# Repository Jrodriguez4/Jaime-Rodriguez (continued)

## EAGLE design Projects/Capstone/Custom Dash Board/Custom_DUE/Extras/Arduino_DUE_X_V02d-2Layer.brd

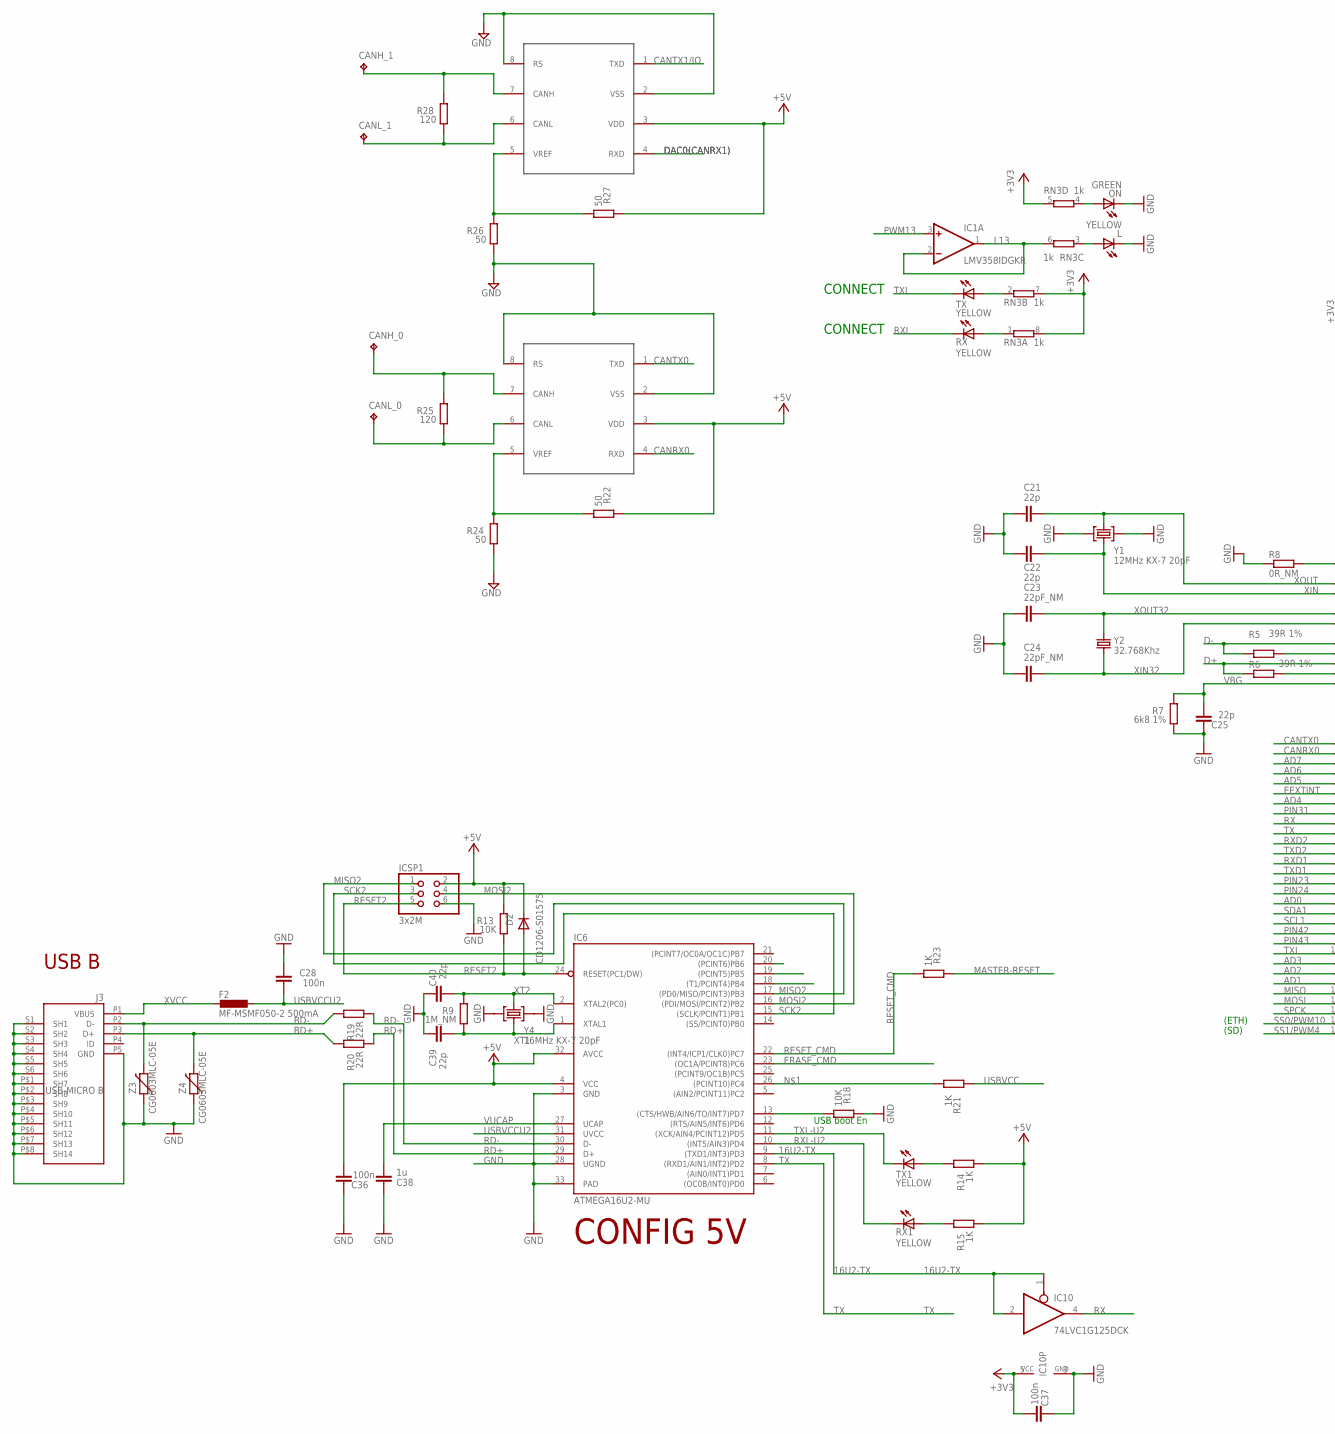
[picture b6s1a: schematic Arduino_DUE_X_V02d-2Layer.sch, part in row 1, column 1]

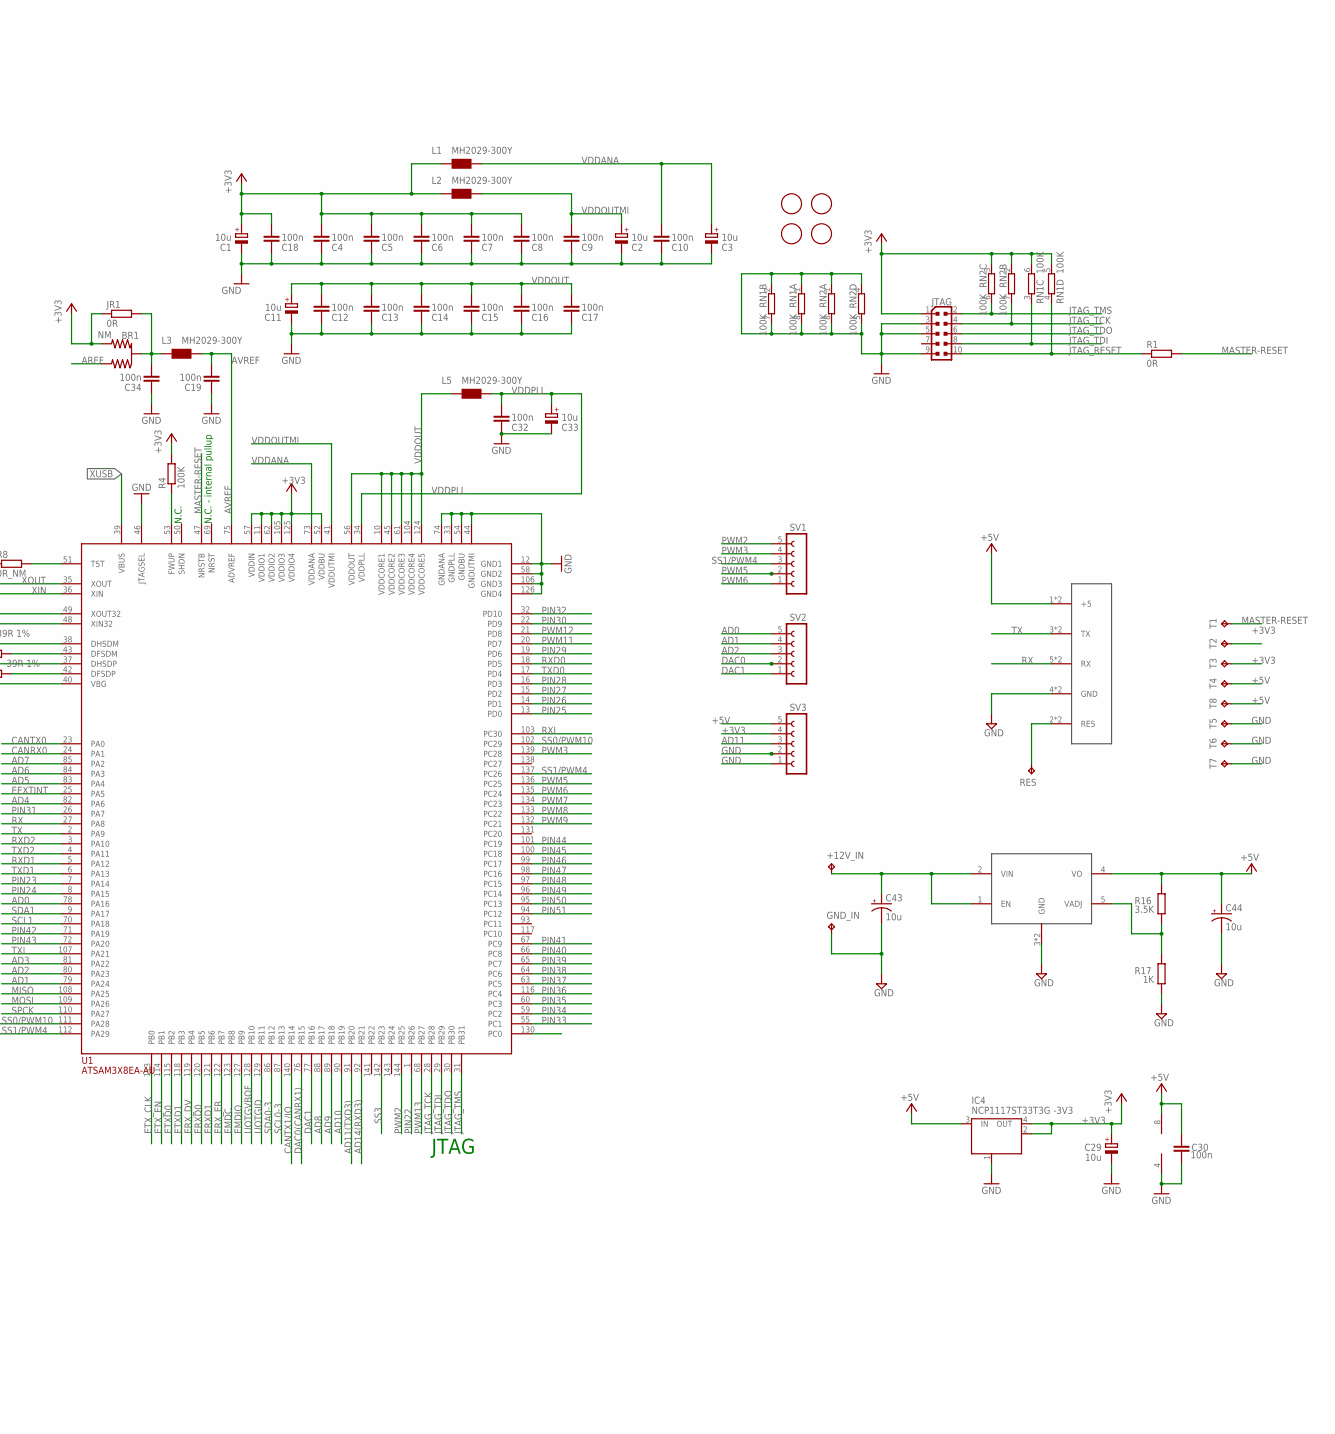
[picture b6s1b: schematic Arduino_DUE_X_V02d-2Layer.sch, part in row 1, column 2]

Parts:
+12V_IN: TPPAD1-13; P1-13
BR1: NM; J0402
C1, C2, C3, C11, C29, C33: 10u; SMC_B
C4, C5, C6, C7, C8, C9, C10, C12, C13, C14, C15, C16, C17, C18, C19, C28, C30, C32, C34, C36, C37: 100n; C0805
C21, C22, C25, C39, C40: 22p; C0805
C23, C24: 22pF_NM; C0805
C38: 1u; C0805
C43, C44: 10u; 153CLV-0405
CANH_0, CANH_1: TPPAD1-13; P1-13
CANL_0, CANL_1: TPPAD1-13; P1-13
D2: CD1206-S01575; MINIMELF
F2: MF-MSMF050-2 500mA; L1812
FID1, FID2, FID3, FID4: FIDUCIALMOUNT; FIDUCIA-MOUNT
GND_IN: TPPAD1-13; P1-13
IC1: LMV358IDGKR; MSOP08
IC4: NCP1117ST33T3G -3V3; SOT223
IC6: ATMEGA16U2-MU; MLF32
IC10: 74LVC1G125DCK; SC70-5
ICSP1: 3x2M; 2X03
J3: USB-MICRO B; CON2_USB_MICRO_B_AT
JR1: 0R; R0805
JTAG: PINHEAD_PINHD-2X5PASSO127; PINHEAD_2X05_127
L: YELLOW; CHIP-LED0805
L1, L2, L3, L5: MH2029-300Y; 0805
ON: GREEN; CHIP-LED0805
R1: 0R; R0805
R4: 100K; R0805
R5, R6: 39R 1%; R0805
R7: 6k8 1%; R0805
R8: 0R_NM; R0805
R9: 1M_NM; R0805
R13, R18: 10K; R0805
R14, R15, R17, R21, R23: 1K; R0805
R16: 3.5K; R0805
R19, R20: 22R; R0805
R22, R24, R26, R27: 50; R0805
R25, R28: 120; R0805
RES: TPB1,27; B1,27
RN1, RN2: 100K; CAT16
RN3: 1k; CAY16
RX, RX1: YELLOW; CHIP-LED0805
SV1, SV2, SV3: FE05-1
T1, T3, T4, T5, T8: TPB1,27; B1,27
T2: TPTP10R; TP10R
T6, T7: TPTP20SQ; TP20SQ
TX, TX1: YELLOW; CHIP-LED0805
U1: ATSAM3X8EA-AU; LQFP144
U2, U4: MCP2551; SOIC8
U3: LCD_DISPLAY; FE05-2
U$1: TLF1963TBATMA1; DPAK
Y1: 12MHz KX-7 20pF; CRYSTAL-3.2-2.5
Y2: 32.768Khz; RESONATOR_EPSON_FC_145
Y4: 16MHz KX-7 20pF; CRYSTAL-3.2-2.5
Z3, Z4: CG0603MLC-05E; CT/CN0805

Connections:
8PB4: IC6.18 ((T1/PCINT4)PB4)
8PB5: IC6.19 ((PCINT5)PB5)
8PB6: IC6.20 ((PCINT6)PB6)
16U2-TX: IC6.9 ((TXD1/INT3)PD3), IC10.1 (OE), IC10.2 (I)
+3V3: BR1.3 (2), C1.+, C4.2, C5.2, C6.2, C7.2, C8.2, C18.2, C29.+, C37.1, IC4.2 (OUT), IC4.4 (OUT), IC10.5 (VCC), JR1.1, JTAG.1, L1.1, L2.1, R4.2, RN1.5 (2), RN1.6 (2), RN2.2 (1), RN2.3 (1), RN3.5 (2), RN3.7 (2), RN3.8 (2), SV3.4, T2.TP, T3.TP, U1.11 (VDDIO1), U1.52 (VDDBU), U1.57 (VDDIN), U1.62 (VDDIO2), U1.105 (VDDIO3), U1.125 (VDDIO4)
+5V: C30.2, C36.1, C44.+, D2.C, IC1.8 (V+), IC4.3 (IN), IC6.4 (VCC), IC6.32 (AVCC), ICSP1.2, R13.2, R14.1, R15.1, R16.2, R22.2, R27.2, SV3.5, T4.TP, T8.TP, U2.3 (VDD), U3.1 (+5), U3.10 (+5), U4.3 (VDD), U$1.4 (VO)
AD0: SV2.5, U1.78 (PA16)
AD1: SV2.4, U1.79 (PA24)
AD2: SV2.3, U1.80 (PA23)
AD3: U1.81 (PA22)
AD4: U1.82 (PA6)
AD5: U1.83 (PA4)
AD6: U1.84 (PA3)
AD7: U1.85 (PA2)
AD8: U1.88 (PB17)
AD9: U1.89 (PB18)
AD10: U1.90 (PB19)
AD11: SV3.3
AD11(TXD3): U1.91 (PB20)
AD14(RXD3): U1.92 (PB21)
AREF: BR1.1
AVREF: C19.2, L3.2, U1.75 (ADVREF)
AVREFL: BR1.2 (C), C34.2, JR1.2, L3.1
BD+: J3.P3 (D+), R20.2, Z4.2
BD-: J3.P2 (D-), R19.2, Z3.2
CANRX0: U1.24 (PA1), U4.4 (RXD)
CANTX0: U1.23 (PA0), U4.1 (TXD)
CANTX1/IO: U1.140 (PB14), U2.1 (TXD)
D+: R6.1, U1.37 (DHSDP)
D-: R5.1, U1.38 (DHSDM)
DAC0: SV2.2
DAC0(CANRX1): U1.76 (PB15), U2.4 (RXD)
DAC1: SV2.1, U1.77 (PB16)
DTR: IC6.13 ((CTS/HWB/AIN6/TO/INT7)PD7), R18.1
EEXTINT: U1.25 (PA5)
EMDC: U1.123 (PB8)
EMDIO: U1.127 (PB9)
ERASE_CMD: IC6.23 ((OC1A/PCINT8)PC6)
ERASE_S: U1.130 (PC0)
ERXD0: U1.120 (PB5)
ERXD1: U1.121 (PB6)
ERX_DV: U1.119 (PB4)
ERX_ER: U1.122 (PB7)
ETXD0: U1.115 (PB2)
ETXD1: U1.118 (PB3)
ETX_CLK: U1.113 (PB0)
ETX_EN: U1.114 (PB1)
GND: C1.-, C2.-, C3.-, C4.1, C5.1, C6.1, C7.1, C8.1, C9.1, C10.1, C11.-, C12.1, C13.1, C14.1, C15.1, C16.1, C17.1, C18.1, C19.1, C21.2, C22.2, C23.2, C24.2, C25.2, C28.2, C29.-, C30.1, C32.1, C33.-, C34.1, C36.2, C37.2, C38.2, C39.2, C40.2, C43.-, C44.-, GND_IN.TP, IC1.4 (V-), IC4.1 (GND/ADJ), IC6.3 (GND), IC6.28 (UGND), IC6.33 (PAD), IC10.3 (GND), ICSP1.6, J3.P5 (GND), J3.P$1 (SH7), J3.P$2 (SH8), J3.P$3 (SH9), J3.P$4 (SH10), J3.P$5 (SH11), J3.P$6 (SH12), J3.P$7 (SH13), J3.P$8 (SH14), J3.S1 (SH1), J3.S2 (SH2), J3.S3 (SH3), J3.S4 (SH4), J3.S5 (SH5), J3.S6 (SH6), JTAG.3, JTAG.5, JTAG.9, L.C, ON.C, R7.1, R8.1, R17.1, R18.2, R24.1, R26.1, RN1.1, RN1.2 (1), RN1.7 (2), RN1.8 (2), RN2.1, RN2.4 (1), RN2.5 (2), RN2.8 (2), SV3.1, SV3.2, T5.TP, T6.TP, T7.TP, U1.12 (GND1), U1.33 (GNDPLL), U1.44 (GNDUTMI), U1.46 (JTAGSEL), U1.54 (GNDBU), U1.58 (GND2), U1.74 (GNDANA), U1.106 (GND3), U1.126 (GND4), U2.2 (VSS), U2.8 (RS), U3.4 (GND), U3.7 (GND), U4.2 (VSS), U4.8 (RS), U$1.3 (GND), U$1.6 (GND), Y1.2 (GND), Y1.4 (GND), Y4.2 (GND), Y4.4 (GND), Z3.1, Z4.1
JTAG_RESET: JTAG.10, R1.1, RN1.4 (1)
JTAG_TCK: JTAG.4, RN2.7 (2), U1.28 (PB28)
JTAG_TDI: JTAG.8, RN1.3 (1), U1.29 (PB29)
JTAG_TDO: JTAG.6, U1.30 (PB30)
JTAG_TMS: JTAG.2, RN2.6 (2), U1.31 (PB31)
L13: IC1.1 (OUT), IC1.2 (-IN), RN3.6 (2)
MASTER-RESET: R1.2, R23.2, T1.TP, U1.47 (NRSTB)
MISO: U1.108 (PA25)
MISO2: IC6.17 ((PD0/MISO/PCINT3)PB3), ICSP1.1
MOSI: U1.109 (PA26)
MOSI2: IC6.16 ((PDI/MOSI/PCINT2)PB2), ICSP1.4
unnamed: IC6.26 ((PCINT10)PC4), R21.1
unnamed: L.A, RN3.3 (1)
unnamed: ON.A, RN3.4 (1)
unnamed: R15.2, RX1.A
unnamed: R8.2, U1.51 (TST)
unnamed: R4.1, U1.53 (FWUP)
unnamed: R5.2, U1.43 (DFSDM)
unnamed: R6.2, U1.42 (DFSDP)
unnamed: +12V_IN.TP, C43.+, U$1.1 (EN), U$1.2 (VIN)
unnamed: R14.2, TX1.A
unnamed: R16.1, R17.2, U$1.5 (VADJ)
unnamed: R26.2, R27.1, U2.5 (VREF)
unnamed: R22.1, R24.2, U4.5 (VREF)
unnamed: CANH_0.TP, R25.2, U4.7 (CANH)
unnamed: CANL_0.TP, R25.1, U4.6 (CANL)
unnamed: RES.TP, U3.2 (RES), U3.9 (RES)
unnamed: CANH_1.TP, R28.2, U2.7 (CANH)
unnamed: CANL_1.TP, R28.1, U2.6 (CANL)
unnamed: RN3.1, RX.A
unnamed: RN3.2 (1), TX.A
PIN22: U1.1 (PB26)
PIN23: U1.7 (PA14)
PIN24: U1.8 (PA15)
PIN25: U1.13 (PD0)
PIN26: U1.14 (PD1)
PIN27: U1.15 (PD2)
PIN28: U1.16 (PD3)
PIN29: U1.19 (PD6)
PIN30: U1.22 (PD9)
PIN31: U1.26 (PA7)
PIN32: U1.32 (PD10)
PIN33: U1.55 (PC1)
PIN34: U1.59 (PC2)
PIN35: U1.60 (PC3)
PIN36: U1.116 (PC4)
PIN37: U1.63 (PC5)
PIN38: U1.64 (PC6)
PIN39: U1.65 (PC7)
PIN40: U1.66 (PC8)
PIN41: U1.67 (PC9)
PIN42: U1.71 (PA19)
PIN43: U1.72 (PA20)
PIN44: U1.101 (PC19)
PIN45: U1.100 (PC18)
PIN46: U1.99 (PC17)
PIN47: U1.98 (PC16)
PIN48: U1.97 (PC15)
PIN49: U1.96 (PC14)
PIN50: U1.95 (PC13)
PIN51: U1.94 (PC12)
PWM2: SV1.5, U1.144 (PB25)
PWM3: SV1.4, U1.139 (PC28)
PWM5: SV1.2, U1.136 (PC25)
PWM6: SV1.1, U1.135 (PC24)
PWM7: U1.134 (PC23)
PWM8: U1.133 (PC22)
PWM9: U1.132 (PC21)
PWM11: U1.20 (PD7)
PWM12: U1.21 (PD8)
PWM13: IC1.3 (+IN), U1.68 (PB27)
RD+: IC6.29 (D+), R20.1
RD-: IC6.30 (D-), R19.1
RESET2: D2.A, IC6.24 (RESET(PC1/DW)), ICSP1.5, R13.1
RESET_CMD: IC6.22 ((INT4/ICP1/CLK0)PC7), R23.1
RX: IC10.4 (O), U1.27 (PA8), U3.5 (RX), U3.6 (RX)
RXD0: U1.18 (PD5)
RXD1: U1.5 (PA12)
RXD2: U1.3 (PA10)
RXL: RX.C, U1.103 (PC30)
RXL-U2: IC6.10 ((INT5/AIN3)PD4), RX1.C
SCK2: IC6.15 ((SCLK/PCINT1)PB1), ICSP1.3
SCL0-3: U1.87 (PB13)
SCL1: U1.70 (PA18)
SDA0-3: U1.86 (PB12)
SDA1: U1.9 (PA17)
SPCK: U1.110 (PA27)
SS0/PWM10: U1.102 (PC29), U1.111 (PA28)
SS1/PWM4: SV1.3, U1.112 (PA29), U1.137 (PC26)
SS3: U1.142 (PB23)
TX: IC6.8 ((RXD1/AIN1/INT2)PD2), U1.2 (PA9), U3.3 (TX), U3.8 (TX)
TXD0: U1.17 (PD4)
TXD1: U1.6 (PA13)
TXD2: U1.4 (PA11)
TXL: TX.C, U1.107 (PA21)
TXL-U2: IC6.11 ((XCK/AIN4/PCINT12)PD5), TX1.C
UOTGID: U1.129 (PB11)
UOTGVBOF: U1.128 (PB10)
USBVCC: R21.2
USBVCCU2: C28.1, F2.1, IC6.31 (UVCC)
VBG: C25.1, R7.2, U1.40 (VBG)
VDDANA: C3.+, C10.2, L1.2, U1.73 (VDDANA)
VDDOUT: C11.+, C12.2, C13.2, C14.2, C15.2, C16.2, C17.2, L5.1, U1.10 (VDDCORE1), U1.45 (VDDCORE2), U1.56 (VDDOUT), U1.61 (VDDCORE3), U1.104 (VDDCORE4), U1.124 (VDDCORE5)
VDDOUTMI: C2.+, C9.2, L2.2, U1.41 (VDDUTMI)
VDDPLL: C32.2, C33.+, L5.2, U1.34 (VDDPLL)
VUCAP: C38.1, IC6.27 (UCAP)
XIN: C22.1, U1.36 (XIN), Y1.1 (C1)
XIN32: C24.1, U1.48 (XIN32), Y2.P$2 (2)
XOUT: C21.1, U1.35 (XOUT), Y1.3 (C2)
XOUT32: C23.1, U1.49 (XOUT32), Y2.P$1 (1)
XT1: C39.1, IC6.1 (XTAL1), R9.1, Y4.1 (C1)
XT2: C40.1, IC6.2 (XTAL2(PC0)), R9.2, Y4.3 (C2)
XUSB: U1.39 (VBUS)
XVCC: F2.2, J3.P1 (VBUS)

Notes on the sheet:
N.C.
JTAG
CONNECT
(ETH)
(SD)
USB boot En
CONFIG 5V
USB B
N.C. - internal pullup

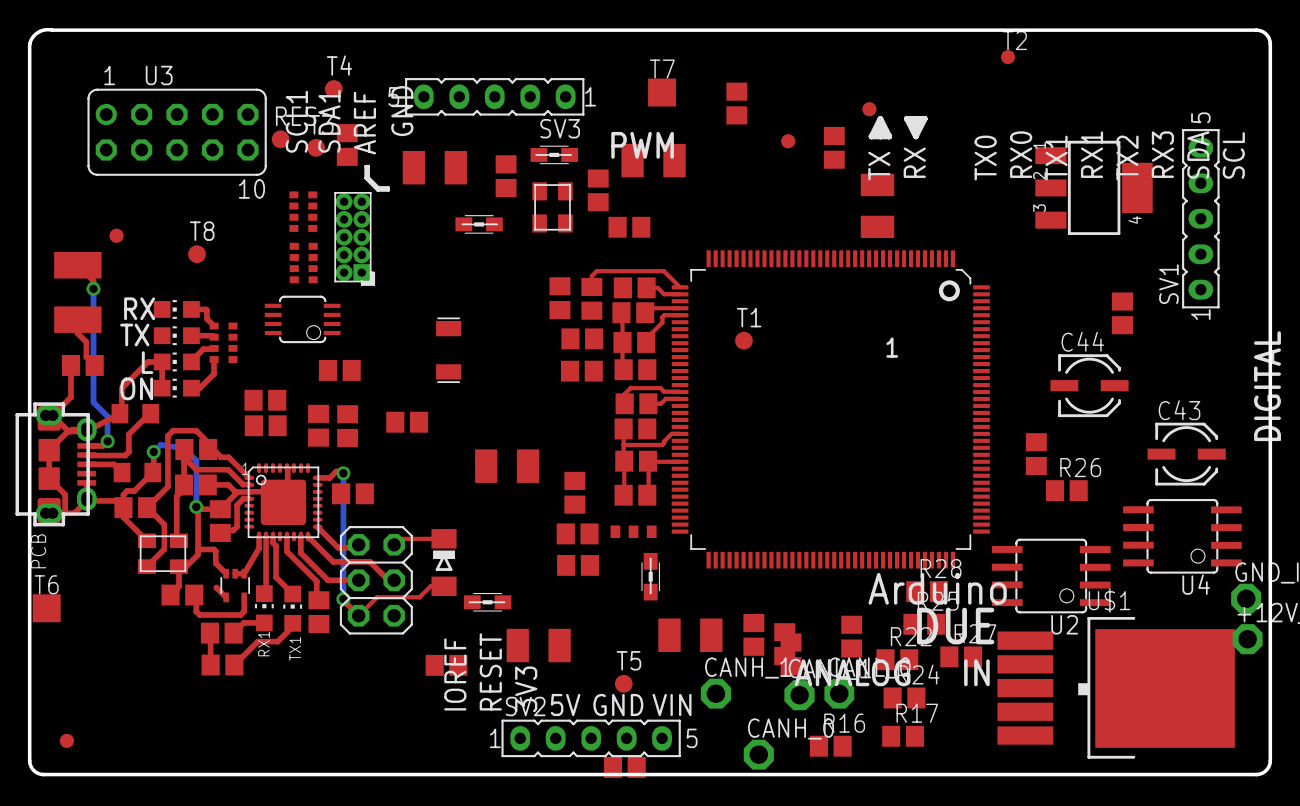
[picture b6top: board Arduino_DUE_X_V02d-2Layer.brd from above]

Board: 2 copper layers, 88.9 x 53.4 mm, 116 parts (0 on the bottom side), 80 nets.

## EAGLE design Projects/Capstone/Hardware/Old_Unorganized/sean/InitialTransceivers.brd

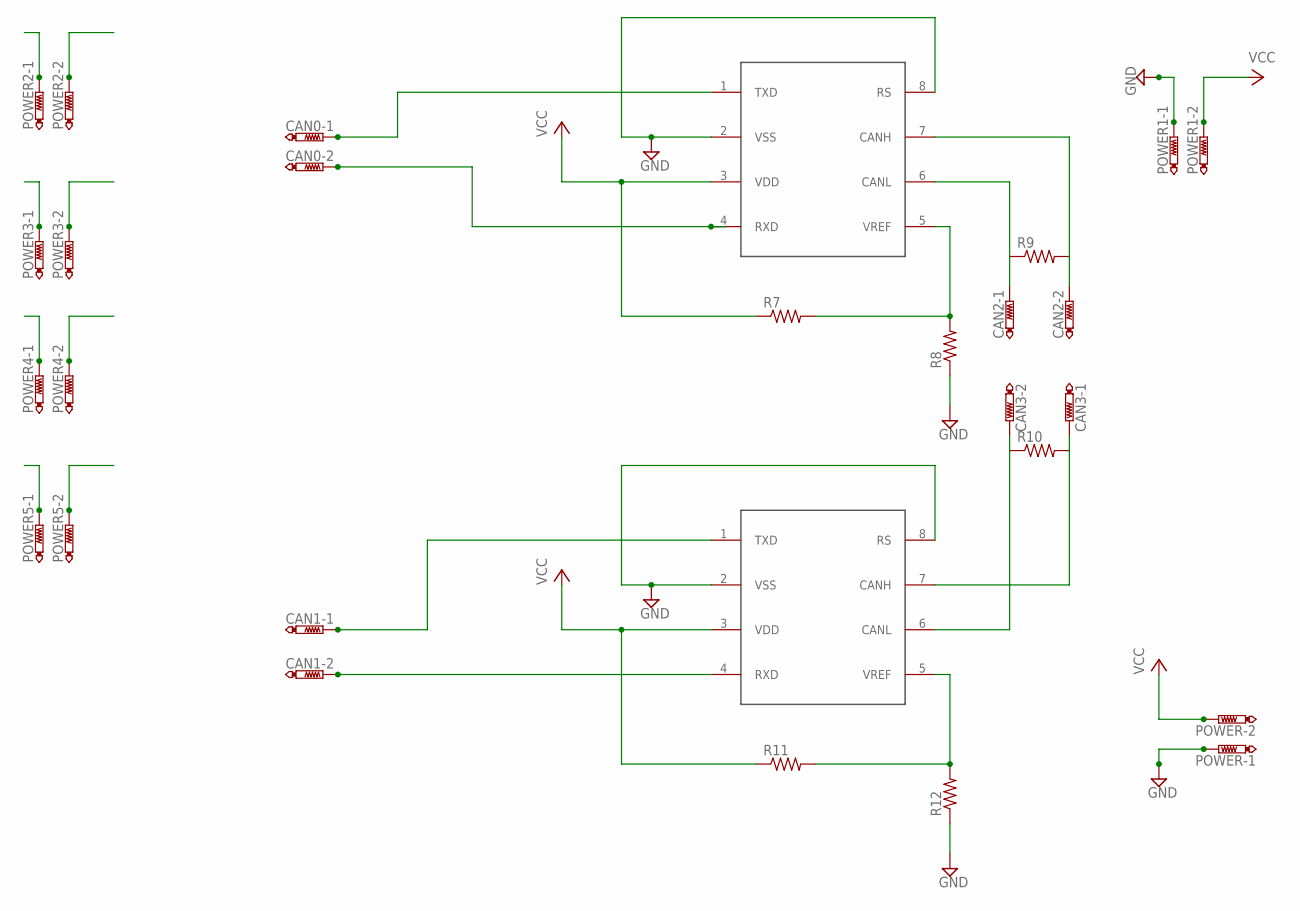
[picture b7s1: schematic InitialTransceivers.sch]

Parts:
CAN0, CAN1, CAN2, CAN3: PTR2; P2-38-17
POWER, POWER1, POWER2, POWER3, POWER4, POWER5: PTR2; P2-38-17
R7, R8, R9, R10, R11, R12: R-US_0204/5; 0204/5
U$2, U$3: MCP2551-DIP; DIL08

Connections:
A0: POWER2.TP-1, POWER3.TP-1
A1: POWER2.TP-2, POWER3.TP-2
A2: POWER4.TP-1, POWER5.TP-1
A3: POWER4.TP-2, POWER5.TP-2
CH: CAN3.TP-1, R10.2, U$3.7 (CANH)
CL: CAN3.TP-2, R10.1, U$3.6 (CANL)
GND: POWER.TP-1, POWER1.TP-1, R8.1, R12.1, U$2.2 (VSS), U$2.8 (RS), U$3.2 (VSS), U$3.8 (RS)
unnamed: CAN2.TP-1, R9.1, U$2.6 (CANL)
unnamed: CAN2.TP-2, R9.2, U$2.7 (CANH)
unnamed: R7.2, R8.2, U$2.5 (VREF)
unnamed: R11.2, R12.2, U$3.5 (VREF)
RX1: CAN0.TP-2, U$2.4 (RXD)
RX2: CAN1.TP-2, U$3.4 (RXD)
TX1: CAN0.TP-1, U$2.1 (TXD)
TX2: CAN1.TP-1, U$3.1 (TXD)
VCC: POWER.TP-2, POWER1.TP-2, R7.1, R11.1, U$2.3 (VDD), U$3.3 (VDD)

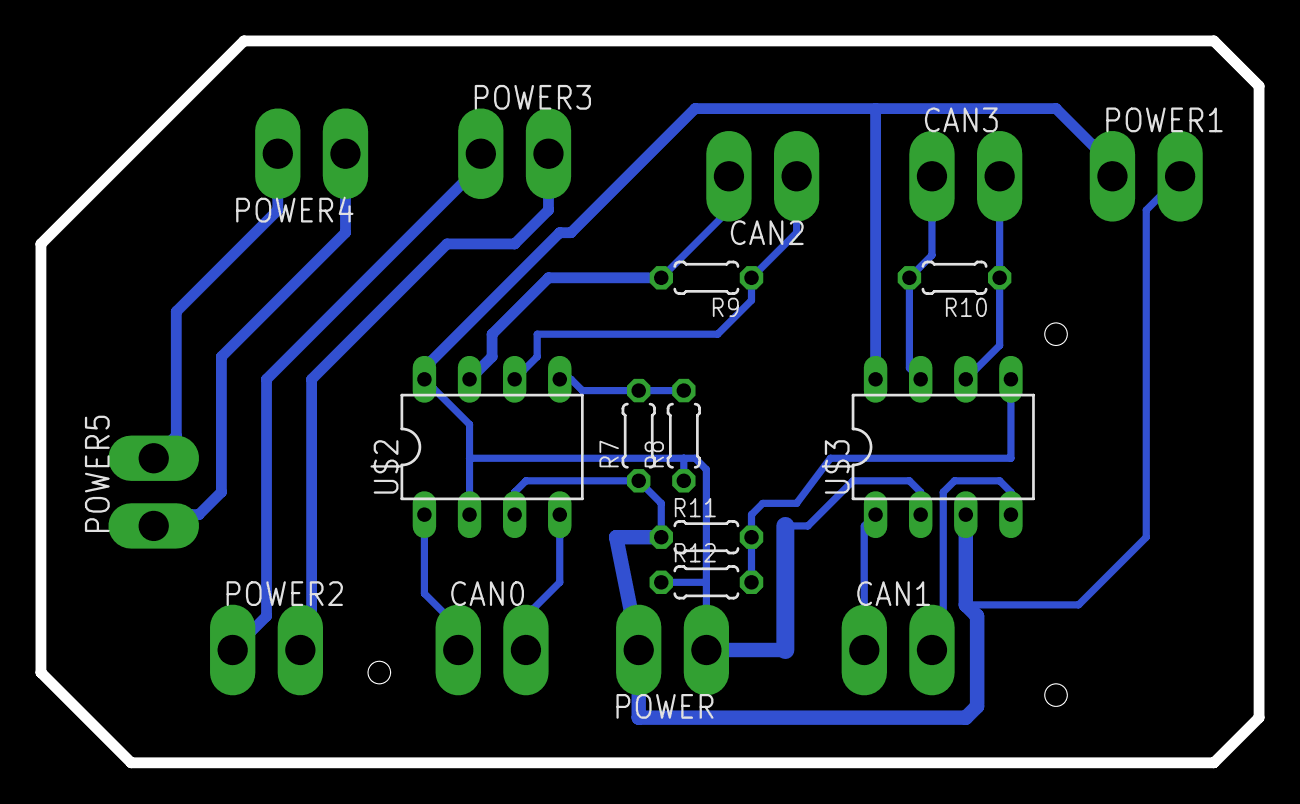
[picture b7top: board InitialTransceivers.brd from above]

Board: 2 copper layers, 68.6 x 40.6 mm, 18 parts (0 on the bottom side), 16 nets.

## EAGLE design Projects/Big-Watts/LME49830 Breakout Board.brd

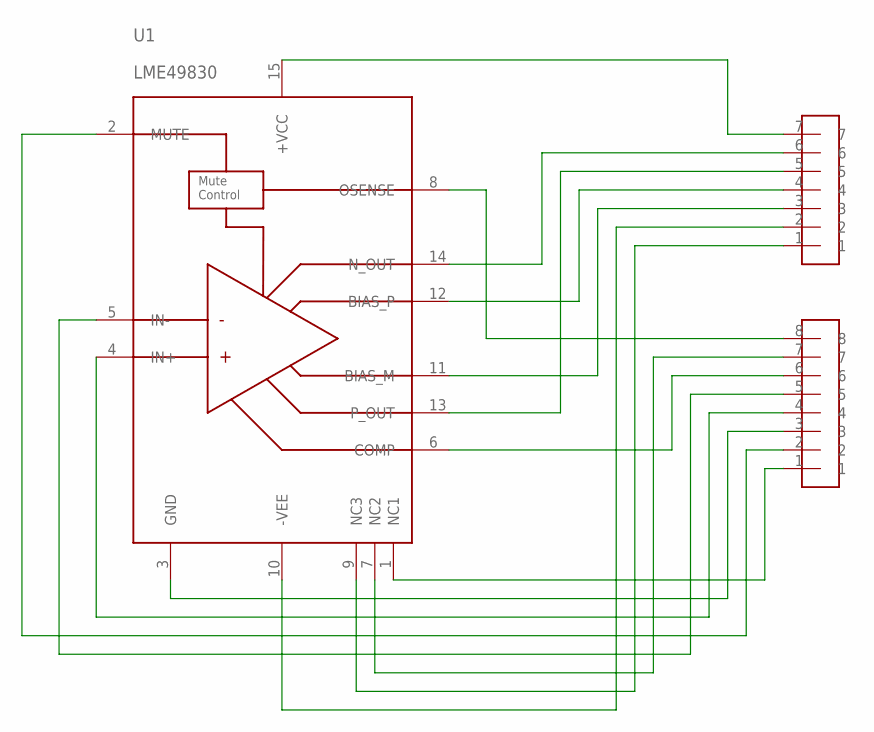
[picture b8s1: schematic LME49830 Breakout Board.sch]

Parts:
U1: LME49830; NDN0015A
U$1: 1X7HEADER_100MIL; 1X7_100MIL
U$2: 1X8HEADER_100MIL; 1X8_100MIL

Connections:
unnamed: U1.1 (NC1), U$2.1
unnamed: U1.2 (MUTE), U$2.2
unnamed: U1.3 (GND), U$2.3
unnamed: U1.4 (IN+), U$2.4
unnamed: U1.5 (IN-), U$2.5
unnamed: U1.6 (COMP), U$2.6
unnamed: U1.7 (NC2), U$2.7
unnamed: U1.8 (OSENSE), U$2.8
unnamed: U1.9 (NC3), U$1.1
unnamed: U1.10 (-VEE), U$1.2
unnamed: U1.11 (BIAS_M), U$1.3
unnamed: U1.12 (BIAS_P), U$1.4
unnamed: U1.13 (P_OUT), U$1.5
unnamed: U1.14 (N_OUT), U$1.6
unnamed: U1.15 (+VCC), U$1.7

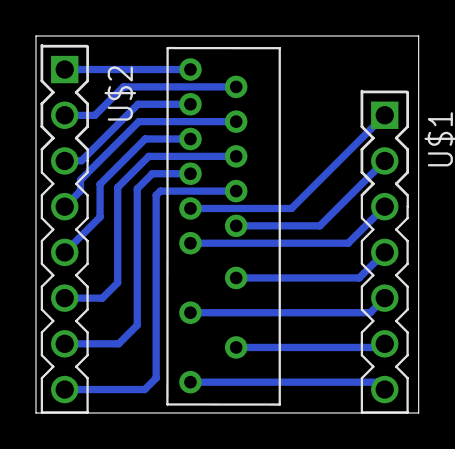
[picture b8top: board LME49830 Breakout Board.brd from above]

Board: 2 copper layers, 21.3 x 20.9 mm, 3 parts (0 on the bottom side), 15 nets.

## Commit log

2015-06-16 Adding projects and resume to create git bio
2015-06-17 Added some images from previous projects
2015-06-17 Added PLL Project from ECE323
2015-06-18 adding dash pics
2015-06-18 added some screenshots
2015-06-18 updated pic
2015-07-03 Added Guitar Pedal Projects
2015-09-30 added ref
